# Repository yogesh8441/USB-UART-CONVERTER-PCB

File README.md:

# USB-UART Converter PCB

## 📌 Overview

This project is a USB-to-UART Converter PCB designed using KiCad. It is used to interface a computer with UART-based embedded systems.

## ✨ Features

- USB to UART Communication
- 2-Layer PCB Design
- Compact PCB Layout
- ERC and DRC Checked
- Manufacturing Ready Gerber Files
- ## 🛠 Software Used

- KiCad 10

## 📂 Project Files

- KiCad Project (.kicad_pro)
- Schematic (.kicad_sch)
- PCB Layout (.kicad_pcb)
- Gerber Files
- Project images
## 📷 Project Images

### Schematic

### PCB Layout

### Top 3D View

### Bottom 3D View

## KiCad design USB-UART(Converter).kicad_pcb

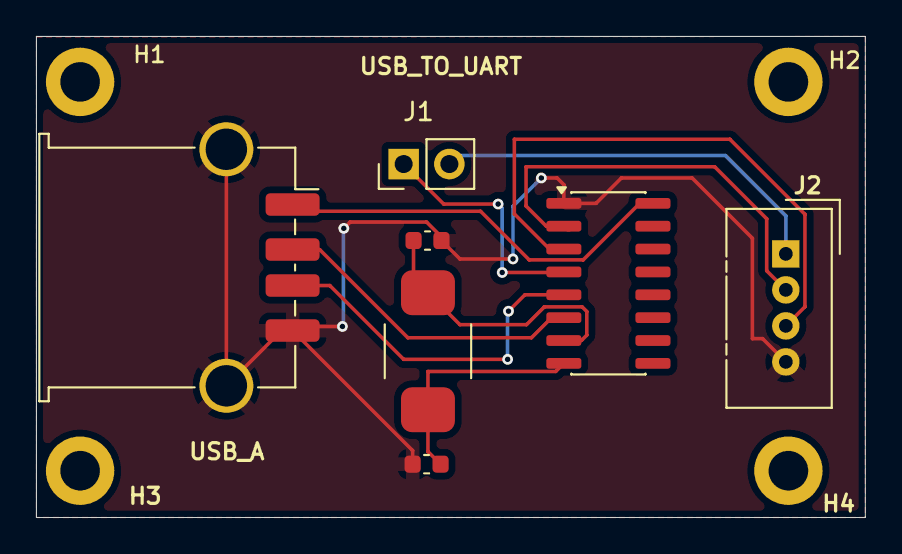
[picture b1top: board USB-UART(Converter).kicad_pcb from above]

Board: 2 copper layers, 46.0 x 26.7 mm, 7 parts (0 on the bottom side), 10 nets.

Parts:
C1, C2: 22uF; C_0603_1608Metric
J1: Conn_01x02_Socket; PinHeader_1x02_P2.54mm_Vertical
J2: Conn_01x04_Pin; NS-Tech_Grove_1x04_P2mm_Vertical
Je1: USB_A; USB_A_TE_292303-7_Horizontal
U1: CH340G; SOIC-16_3.9x9.9mm_P1.27mm
Y1: Crystal; Crystal_SMD_TXC_AX_8045-2Pin_8.0x4.5mm

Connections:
/3V3: J1.1, U1.4 (V3)
/3V3_O/P: J1.2, J2.1
/RX: J2.3, U1.3 (RXD)
/TX: J2.2, U1.2 (TXD)
/V_BUS(5V): Je1.1 (VBUS), U1.16 (VCC)
/XI: C1.1, U1.7 (XI), Y1.1
/XO: C2.1, U1.8 (XO), Y1.2
GND: C1.2, C2.2, J2.4, Je1.4 (GND), Je1.SH (Shield), U1.1 (GND)
unnamed: Je1.3 (D+), U1.5 (UD+)
unnamed: Je1.2 (D-), U1.6 (UD-)
